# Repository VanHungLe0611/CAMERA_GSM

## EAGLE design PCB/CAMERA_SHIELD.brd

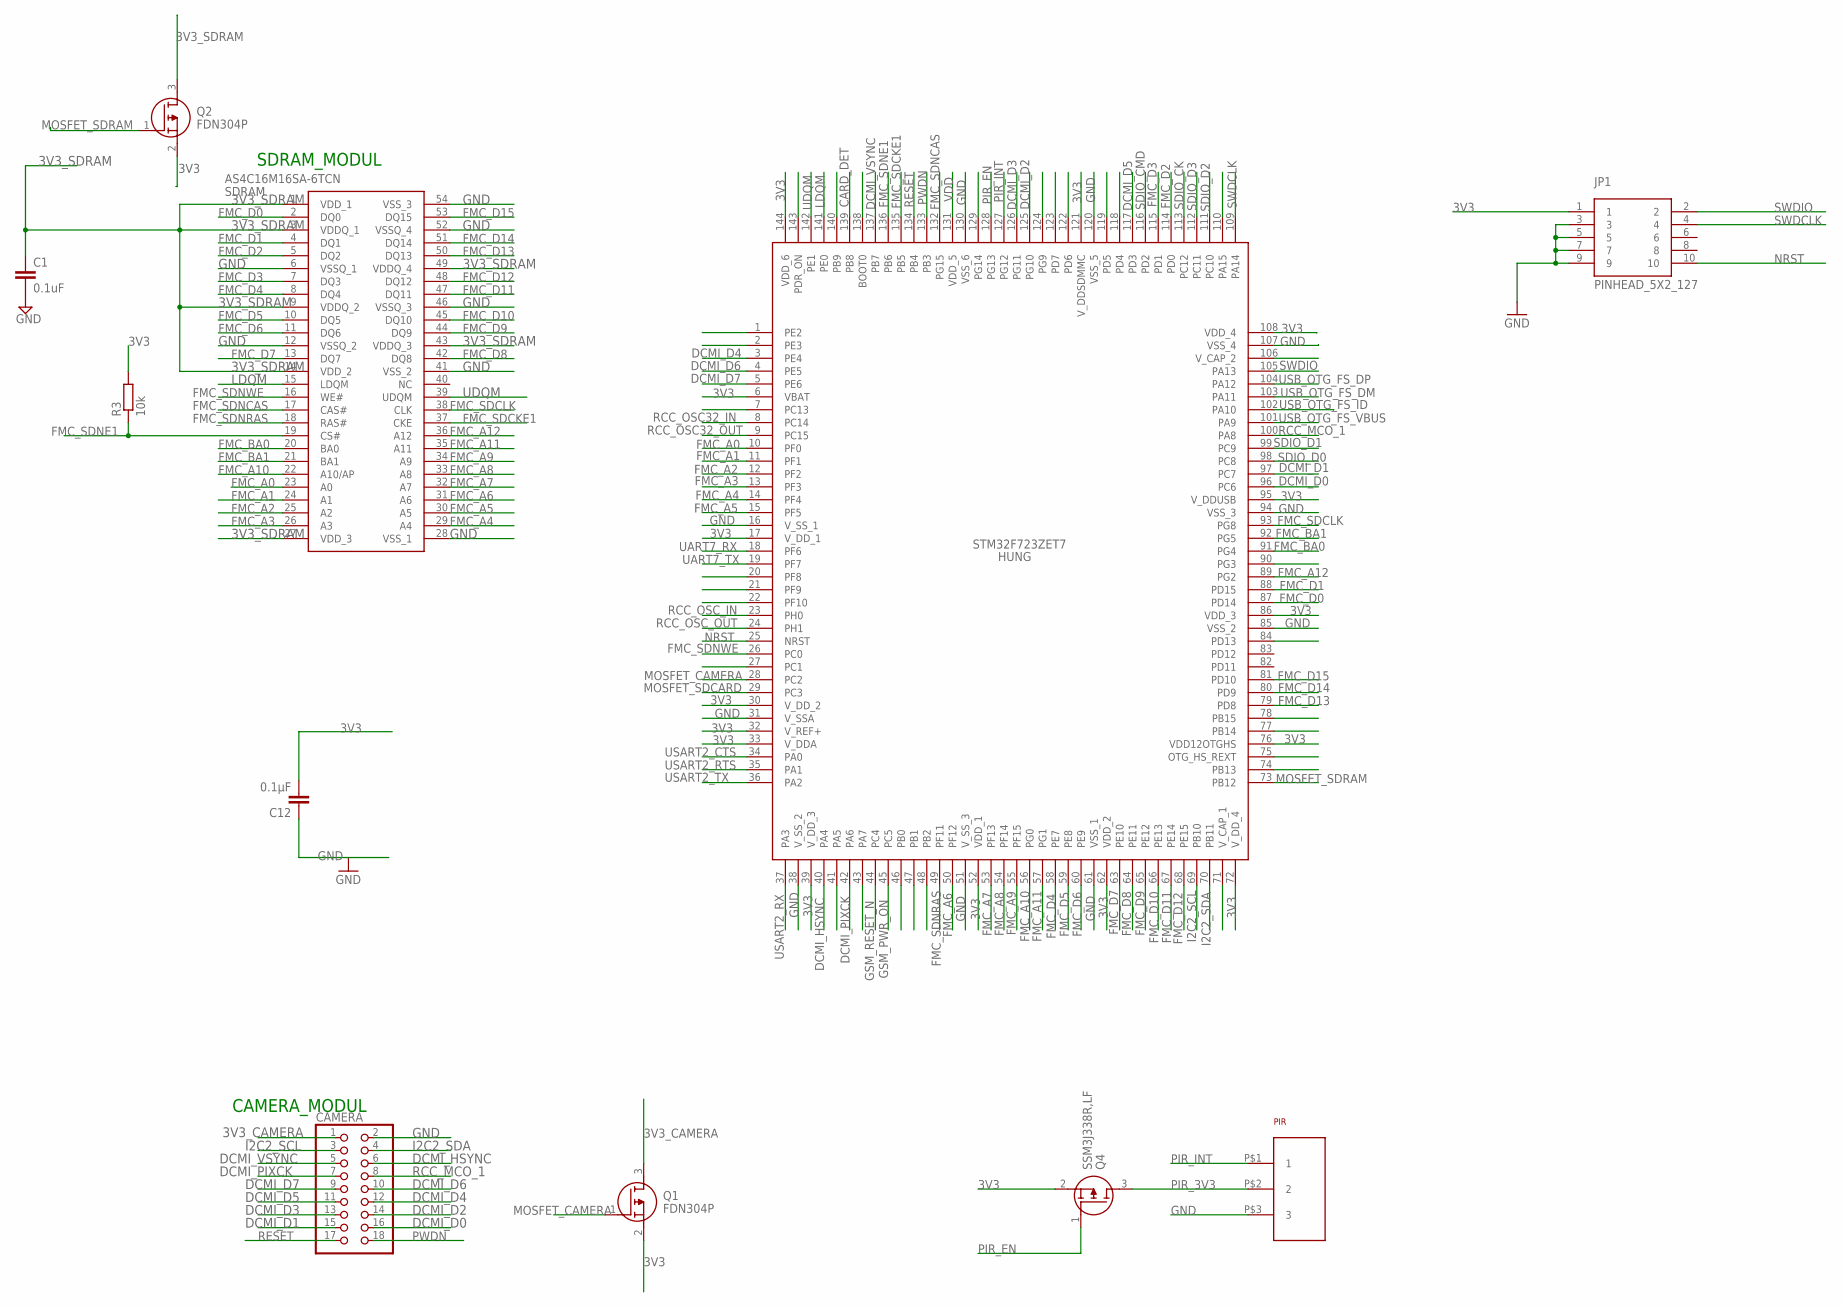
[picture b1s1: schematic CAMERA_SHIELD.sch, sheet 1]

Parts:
C1: 0.1uF; C0402K
C12: 0.1µF; C0402K
CAMERA: 0; 2X09
HUNG: STM32F723ZET7; QFP50P2200X2200X160-144N
JP1: PINHEAD_5X2_127; PINHEAD_2X5_127
PIR: SENBA_PIR_3PIN; SENBA_PIR
Q1, Q2: FDN304P; SOT95P237X112-3N
Q4: SSM3J338R,LF; SSM3J332RLFT
R3: 10k; C0402K
SDRAM: AS4C16M16SA-6TCN; SOP80P1176X120-54N

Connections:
3V3: C12.2, HUNG.6 (VBAT), HUNG.17 (V_DD_1), HUNG.30 (V_DD_2), HUNG.32 (V_REF+), HUNG.33 (V_DDA), HUNG.39 (V_DD_3), HUNG.52 (VDD_1), HUNG.62 (VDD_2), HUNG.72 (V_DD_4), HUNG.76 (VDD12OTGHS), HUNG.86 (VDD_3), HUNG.95 (V_DDUSB), HUNG.108 (VDD_4), HUNG.121 (V_DDSDMMC), HUNG.144 (VDD_6), JP1.1, Q1.2 (S), Q2.2 (S), Q4.2 (S), R3.2; also elsewhere on the board
3V3_CAMERA: CAMERA.1, Q1.3 (D)
3V3_SDRAM: C1.1, Q2.3 (D), SDRAM.1 (VDD_1), SDRAM.3 (VDDQ_1), SDRAM.9 (VDDQ_2), SDRAM.14 (VDD_2), SDRAM.27 (VDD_3), SDRAM.43 (VDDQ_3), SDRAM.49 (VDDQ_4)
CARD_DET: HUNG.139 (PB8); also elsewhere on the board
DCMI_D0: CAMERA.16, HUNG.96 (PC6)
DCMI_D1: CAMERA.15, HUNG.97 (PC7)
DCMI_D2: CAMERA.14, HUNG.125 (PG10)
DCMI_D3: CAMERA.13, HUNG.126 (PG11)
DCMI_D4: CAMERA.12, HUNG.3 (PE4)
DCMI_D5: CAMERA.11, HUNG.117 (PD3)
DCMI_D6: CAMERA.10, HUNG.4 (PE5)
DCMI_D7: CAMERA.9, HUNG.5 (PE6)
DCMI_HSYNC: CAMERA.6, HUNG.40 (PA4)
DCMI_PIXCK: CAMERA.7, HUNG.42 (PA6)
DCMI_VSYNC: CAMERA.5, HUNG.137 (PB7)
FMC_A0: HUNG.10 (PF0), SDRAM.23 (A0)
FMC_A1: HUNG.11 (PF1), SDRAM.24 (A1)
FMC_A2: HUNG.12 (PF2), SDRAM.25 (A2)
FMC_A3: HUNG.13 (PF3), SDRAM.26 (A3)
FMC_A4: HUNG.14 (PF4), SDRAM.29 (A4)
FMC_A5: HUNG.15 (PF5), SDRAM.30 (A5)
FMC_A6: HUNG.50 (PF12), SDRAM.31 (A6)
FMC_A7: HUNG.53 (PF13), SDRAM.32 (A7)
FMC_A8: HUNG.54 (PF14), SDRAM.33 (A8)
FMC_A9: HUNG.55 (PF15), SDRAM.34 (A9)
FMC_A10: HUNG.56 (PG0), SDRAM.22 (A10/AP)
FMC_A11: HUNG.57 (PG1), SDRAM.35 (A11)
FMC_A12: HUNG.89 (PG2), SDRAM.36 (A12)
FMC_BA0: HUNG.91 (PG4), SDRAM.20 (BA0)
FMC_BA1: HUNG.92 (PG5), SDRAM.21 (BA1)
FMC_D0: HUNG.87 (PD14), SDRAM.2 (DQ0)
FMC_D1: HUNG.88 (PD15), SDRAM.4 (DQ1)
FMC_D2: HUNG.114 (PD0), SDRAM.5 (DQ2)
FMC_D3: HUNG.115 (PD1), SDRAM.7 (DQ3)
FMC_D4: HUNG.58 (PE7), SDRAM.8 (DQ4)
FMC_D5: HUNG.59 (PE8), SDRAM.10 (DQ5)
FMC_D6: HUNG.60 (PE9), SDRAM.11 (DQ6)
FMC_D7: HUNG.63 (PE10), SDRAM.13 (DQ7)
FMC_D8: HUNG.64 (PE11), SDRAM.42 (DQ8)
FMC_D9: HUNG.65 (PE12), SDRAM.44 (DQ9)
FMC_D10: HUNG.66 (PE13), SDRAM.45 (DQ10)
FMC_D11: HUNG.67 (PE14), SDRAM.47 (DQ11)
FMC_D12: HUNG.68 (PE15), SDRAM.48 (DQ12)
FMC_D13: HUNG.79 (PD8), SDRAM.50 (DQ13)
FMC_D14: HUNG.80 (PD9), SDRAM.51 (DQ14)
FMC_D15: HUNG.81 (PD10), SDRAM.53 (DQ15)
FMC_SDCKE1: HUNG.135 (PB5), SDRAM.37 (CKE)
FMC_SDCLK: HUNG.93 (PG8), SDRAM.38 (CLK)
FMC_SDNCAS: HUNG.132 (PG15), SDRAM.17 (CAS#)
FMC_SDNE1: HUNG.136 (PB6), R3.1, SDRAM.19 (CS#)
FMC_SDNRAS: HUNG.49 (PF11), SDRAM.18 (RAS#)
FMC_SDNWE: HUNG.26 (PC0), SDRAM.16 (WE#)
GND: C1.2, C12.1, CAMERA.2, HUNG.16 (V_SS_1), HUNG.31 (V_SSA), HUNG.38 (V_SS_2), HUNG.51 (V_SS_3), HUNG.61 (VSS_1), HUNG.85 (VSS_2), HUNG.94 (VSS_3), HUNG.107 (VSS_4), HUNG.120 (VSS_5), HUNG.130 (VSS_6), JP1.3, JP1.5, JP1.7, JP1.9, PIR.P$3 (3), SDRAM.6 (VSSQ_1), SDRAM.12 (VSSQ_2), SDRAM.28 (VSS_1), SDRAM.41 (VSS_2), SDRAM.46 (VSSQ_3), SDRAM.52 (VSSQ_4), SDRAM.54 (VSS_3); also elsewhere on the board
GSM_PWR_ON: HUNG.45 (PC5); also elsewhere on the board
GSM_RESET_N: HUNG.44 (PC4); also elsewhere on the board
I2C2_SCL: CAMERA.3, HUNG.69 (PB10); also elsewhere on the board
I2C2_SDA: CAMERA.4, HUNG.70 (PB11); also elsewhere on the board
LDQM: HUNG.141 (PE0), SDRAM.15 (LDQM)
MOSFET_CAMERA: HUNG.28 (PC2), Q1.1 (G)
MOSFET_SDCARD: HUNG.29 (PC3); also elsewhere on the board
MOSFET_SDRAM: HUNG.73 (PB12), Q2.1 (G)
NRST: HUNG.25 (NRST), JP1.10
PIR_3V3: PIR.P$2 (2), Q4.3 (D)
PIR_EN: HUNG.128 (PG13), Q4.1 (G)
PIR_INT: HUNG.127 (PG12), PIR.P$1 (1)
PWDN: CAMERA.18, HUNG.133 (PB3)
RCC_MCO_1: CAMERA.8, HUNG.100 (PA8)
RCC_OSC32_IN: HUNG.8 (PC14); also elsewhere on the board
RCC_OSC32_OUT: HUNG.9 (PC15); also elsewhere on the board
RCC_OSC_IN: HUNG.23 (PH0); also elsewhere on the board
RCC_OSC_OUT: HUNG.24 (PH1); also elsewhere on the board
RESET: CAMERA.17, HUNG.134 (PB4)
SDIO_CK: HUNG.113 (PC12); also elsewhere on the board
SDIO_CMD: HUNG.116 (PD2); also elsewhere on the board
SDIO_D0: HUNG.98 (PC8); also elsewhere on the board
SDIO_D1: HUNG.99 (PC9); also elsewhere on the board
SDIO_D2: HUNG.111 (PC10); also elsewhere on the board
SDIO_D3: HUNG.112 (PC11); also elsewhere on the board
SWDCLK: HUNG.109 (PA14), JP1.4
SWDIO: HUNG.105 (PA13), JP1.2
UART7_RX: HUNG.18 (PF6); also elsewhere on the board
UART7_TX: HUNG.19 (PF7); also elsewhere on the board
UDQM: HUNG.142 (PE1), SDRAM.39 (UDQM)
USART2_CTS: HUNG.34 (PA0); also elsewhere on the board
USART2_RTS: HUNG.35 (PA1); also elsewhere on the board
USART2_RX: HUNG.37 (PA3); also elsewhere on the board
USART2_TX: HUNG.36 (PA2); also elsewhere on the board
USB_OTG_FS_DM: HUNG.103 (PA11); also elsewhere on the board
USB_OTG_FS_DP: HUNG.104 (PA12); also elsewhere on the board
USB_OTG_FS_ID: HUNG.102 (PA10); also elsewhere on the board
USB_OTG_FS_VBUS: HUNG.101 (PA9); also elsewhere on the board
VDD: HUNG.131 (VDD_5)

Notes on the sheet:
SDRAM_MODUL
CAMERA_MODUL

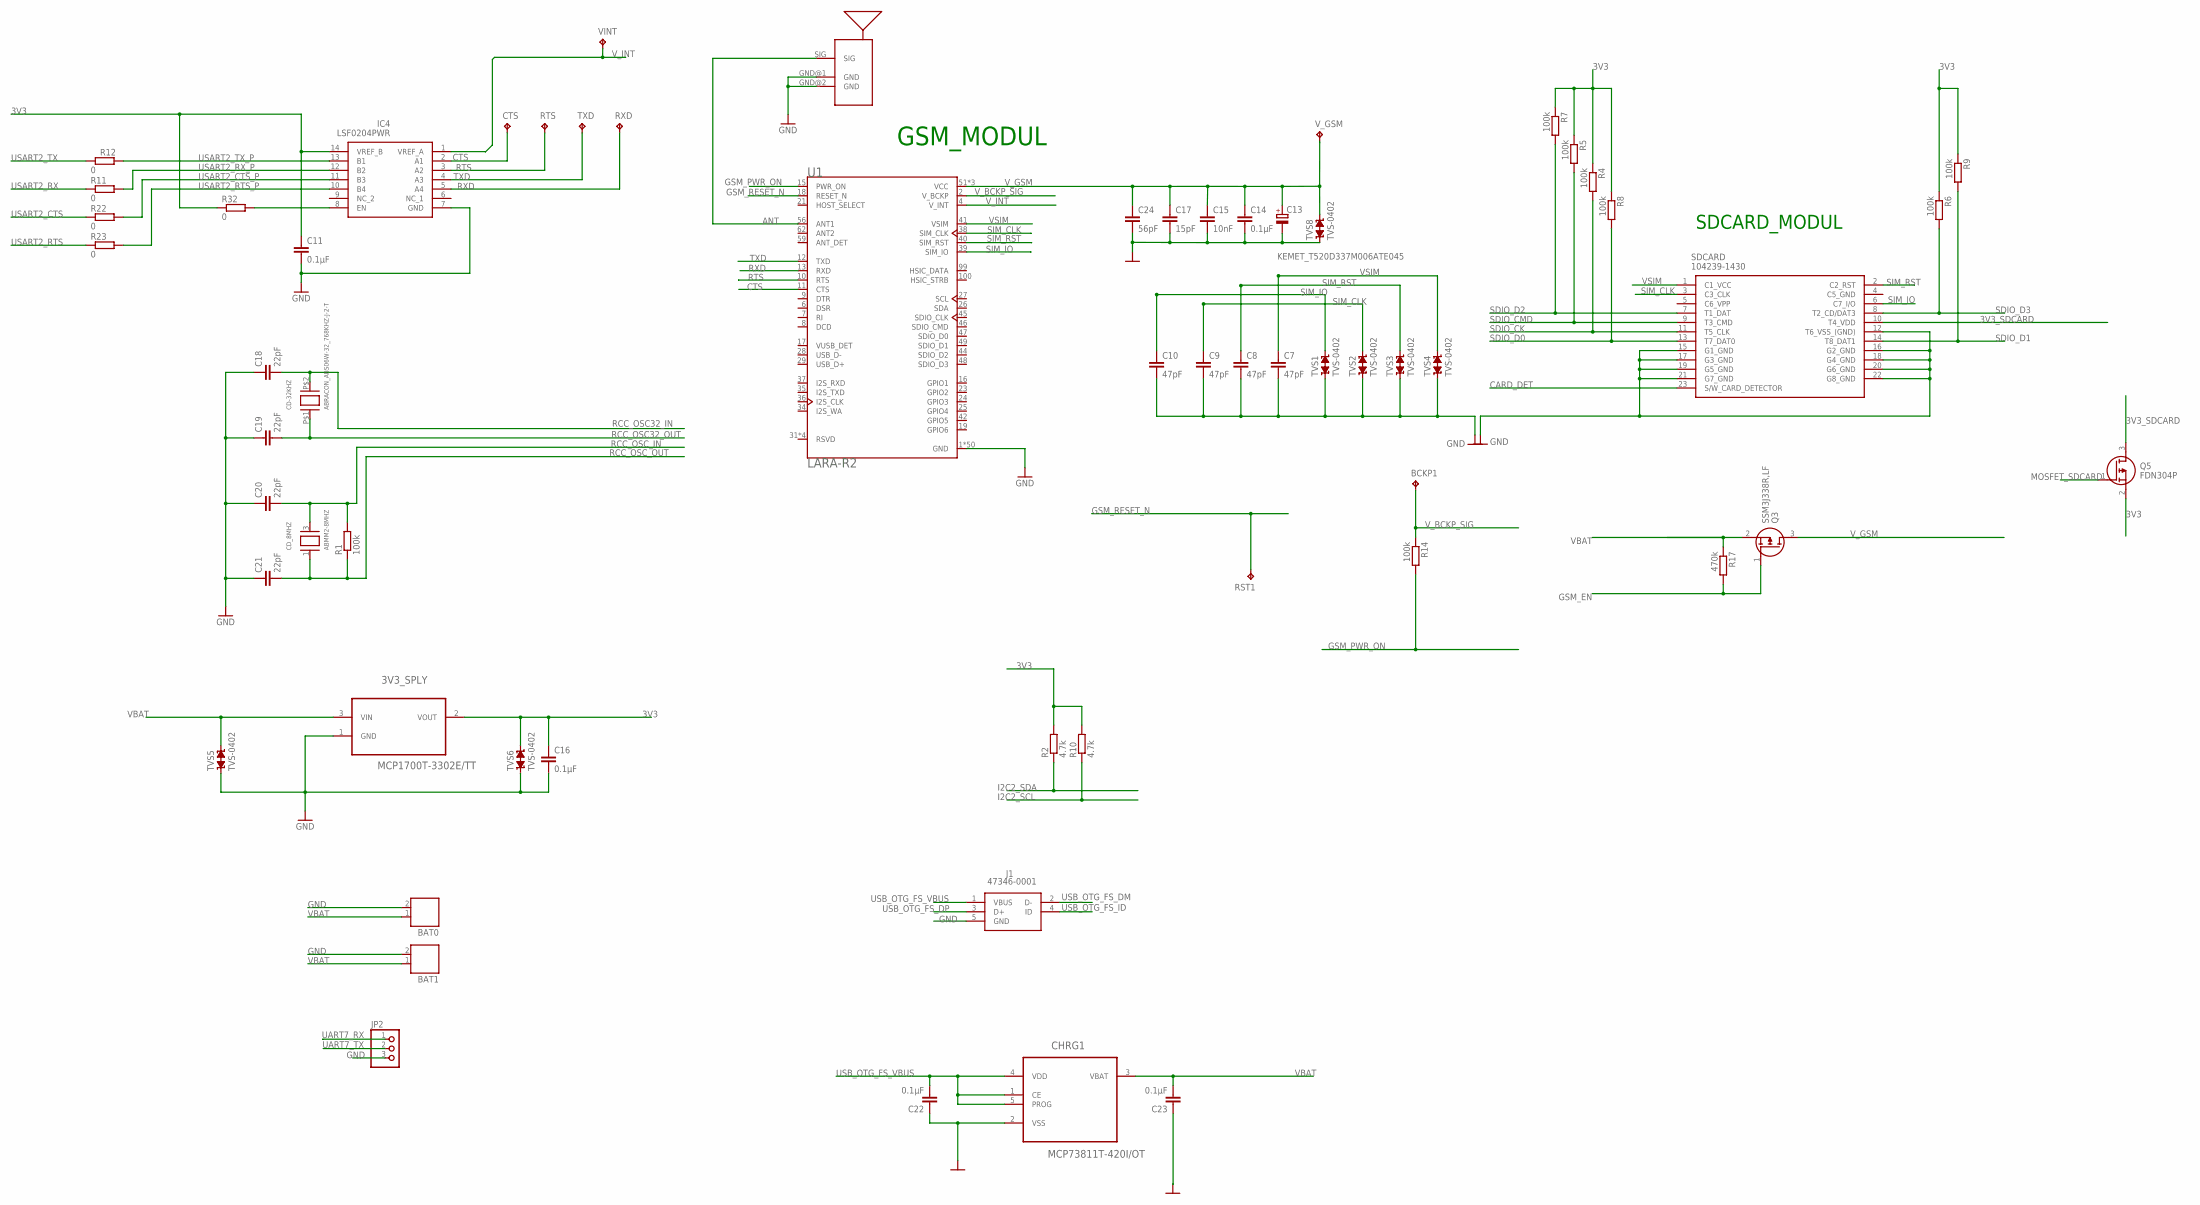
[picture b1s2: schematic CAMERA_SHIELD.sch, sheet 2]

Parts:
3V3_SPLY: MCP1700T-3302E/TT; SOT23
ANT2: U.FL-R-SMT-1; UFL_HIROSE
BAT0, BAT1: JST-PH2
BCKP1: TPB1,27; B1,27
C7, C8, C9, C10: 47pF; C0402K
C11, C14, C16, C22, C23: 0.1µF; C0402K
C13: KEMET_T520D337M006ATE045; 7343_METRIC
C15: 10nF; C0402K
C17: 15pF; C0402K
C18, C19, C20, C21: 22pF; C0402K
C24: 56pF; C0402K
CD-32KHZ: ABRACON_ABS06W-32_768KHZ-J-2-T; 2MM_X_1_2MM
CD_8MHZ: ABMM2-8MHZ; CRYSTAL_ABRACON_6MM_3.6MM
CHRG1: MCP73811T-420I/OT; SOT23-5
CTS: TPB1,27; B1,27
IC4: LSF0204PWR; SOP65P640X120-14N
J1: 47346-0001
JP2: PINHD-1X3; 1X03
Q3: SSM3J338R,LF; SSM3J332RLFT
Q5: FDN304P; SOT95P237X112-3N
R1: 100k; C0402K
R2, R10: 4.7k; C0402K
R4, R5, R6, R7, R8, R9, R14: 100k; R0402
R11, R12, R22, R23: 0; R0402
R17: 470k; R0402
R32: 0; C0402K
RST1: TPB1,27; B1,27
RTS: TPB1,27; B1,27
RXD: TPB1,27; B1,27
SDCARD: 104239-1430; 1042391430
TVS1, TVS2, TVS3, TVS4, TVS5, TVS6, TVS8: TVS-0402; TVS0402
TXD: TPB1,27; B1,27
U1: LARA-R2; XCVR_LARA-R2
VINT: TPB1,27; B1,27
V_GSM: TPB1,27; B1,27

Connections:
3V3: 3V3_SPLY.2 (VOUT), C11.1, C16.1, IC4.14 (VREF_B), Q5.2 (S), R2.2, R4.1, R5.1, R6.1, R7.1, R8.1, R9.1, R10.2, R32.1, TVS6.2; also elsewhere on the board
3V3_SDCARD: Q5.3 (D), SDCARD.10 (T4_VDD)
ANT: ANT2.SIG, U1.56 (ANT1)
CARD_DET: SDCARD.23 (S/W_CARD_DETECTOR); also elsewhere on the board
CTS: CTS.TP, IC4.2 (A1), U1.11 (CTS)
GND: 3V3_SPLY.1 (GND), ANT2.GND@1 (GND), ANT2.GND@2 (GND), BAT0.2, BAT1.2, C7.2, C8.2, C9.2, C10.2, C11.2, C13.-, C14.2, C15.2, C16.2, C17.2, C18.1, C19.1, C20.1, C21.1, C22.1, C23.1, C24.2, CHRG1.2 (VSS), IC4.7 (GND), J1.5 (GND), JP2.3, SDCARD.12 (T6_VSS_(GND)), SDCARD.15 (G1_GND), SDCARD.16 (G2_GND), SDCARD.17 (G3_GND), SDCARD.18 (G4_GND), SDCARD.19 (G5_GND), SDCARD.20 (G6_GND), SDCARD.21 (G7_GND), SDCARD.22 (G8_GND), TVS1.1, TVS2.1, TVS3.1, TVS4.1, TVS5.1, TVS6.1, TVS8.1, U1.1 (GND), U1.3 (GND), U1.5 (GND), U1.14 (GND), U1.20 (GND), U1.22 (GND), U1.30 (GND), U1.32 (GND), U1.43 (GND), U1.50 (GND), U1.54 (GND), U1.55 (GND), U1.57 (GND), U1.58 (GND), U1.60 (GND), U1.61 (GND), U1.63 (GND), U1.64 (GND), U1.65 (GND), U1.66 (GND), U1.67 (GND), U1.68 (GND), U1.69 (GND), U1.70 (GND), U1.71 (GND), U1.72 (GND), U1.73 (GND), U1.74 (GND), U1.75 (GND), U1.76 (GND), U1.77 (GND), U1.78 (GND), U1.79 (GND), U1.80 (GND), U1.81 (GND), U1.82 (GND), U1.83 (GND), U1.84 (GND), U1.85 (GND), U1.86 (GND), U1.87 (GND), U1.88 (GND), U1.89 (GND), U1.90 (GND), U1.91 (GND), U1.92 (GND), U1.93 (GND), U1.94 (GND), U1.95 (GND), U1.96 (GND); also elsewhere on the board
GSM_EN: Q3.1 (G), R17.2
GSM_PWR_ON: R14.2, U1.15 (PWR_ON); also elsewhere on the board
GSM_RESET_N: RST1.TP, U1.18 (RESET_N); also elsewhere on the board
I2C2_SCL: R10.1; also elsewhere on the board
I2C2_SDA: R2.1; also elsewhere on the board
MOSFET_SDCARD: Q5.1 (G); also elsewhere on the board
unnamed: IC4.8 (EN), R32.2
RCC_OSC32_IN: C18.2, CD-32KHZ.P$2 (C1); also elsewhere on the board
RCC_OSC32_OUT: C19.2, CD-32KHZ.P$1 (C0); also elsewhere on the board
RCC_OSC_IN: C20.2, CD_8MHZ.3 (C1), R1.2; also elsewhere on the board
RCC_OSC_OUT: C21.2, CD_8MHZ.1 (C0), R1.1; also elsewhere on the board
RTS: IC4.3 (A2), RTS.TP, U1.10 (RTS)
RXD: IC4.5 (A4), RXD.TP, U1.13 (RXD)
SDIO_CK: R4.2, SDCARD.11 (T5_CLK); also elsewhere on the board
SDIO_CMD: R5.2, SDCARD.9 (T3_CMD); also elsewhere on the board
SDIO_D0: R8.2, SDCARD.13 (T7_DAT0); also elsewhere on the board
SDIO_D1: R9.2, SDCARD.14 (T8_DAT1); also elsewhere on the board
SDIO_D2: R7.2, SDCARD.7 (T1_DAT); also elsewhere on the board
SDIO_D3: R6.2, SDCARD.8 (T2_CD/DAT3); also elsewhere on the board
SIM_CLK: C9.1, SDCARD.3 (C3_CLK), TVS2.2, U1.38 (SIM_CLK)
SIM_IO: C10.1, SDCARD.6 (C7_I/O), TVS1.2, U1.39 (SIM_IO)
SIM_RST: C8.1, SDCARD.2 (C2_RST), TVS3.2, U1.40 (SIM_RST)
TXD: IC4.4 (A3), TXD.TP, U1.12 (TXD)
UART7_RX: JP2.1; also elsewhere on the board
UART7_TX: JP2.2; also elsewhere on the board
USART2_CTS: R22.1; also elsewhere on the board
USART2_CTS_P: IC4.11 (B3), R22.2
USART2_RTS: R23.1; also elsewhere on the board
USART2_RTS_P: IC4.10 (B4), R23.2
USART2_RX: R11.1; also elsewhere on the board
USART2_RX_P: IC4.12 (B2), R11.2
USART2_TX: R12.1; also elsewhere on the board
USART2_TX_P: IC4.13 (B1), R12.2
USB_OTG_FS_DM: J1.2 (D-); also elsewhere on the board
USB_OTG_FS_DP: J1.3 (D+); also elsewhere on the board
USB_OTG_FS_ID: J1.4 (ID); also elsewhere on the board
USB_OTG_FS_VBUS: C22.2, CHRG1.1 (CE), CHRG1.4 (VDD), CHRG1.5 (PROG), J1.1 (VBUS); also elsewhere on the board
VBAT: 3V3_SPLY.3 (VIN), BAT0.1, BAT1.1, C23.2, CHRG1.3 (VBAT), Q3.2 (S), R17.1, TVS5.2
VSIM: C7.1, SDCARD.1 (C1_VCC), TVS4.2, U1.41 (VSIM)
V_BCKP_SIG: BCKP1.TP, R14.1, U1.2 (V_BCKP)
V_GSM: C13.+, C14.1, C15.1, C17.1, C24.1, Q3.3 (D), TVS8.2, U1.51 (VCC), U1.52 (VCC), U1.53 (VCC), V_GSM.TP
V_INT: IC4.1 (VREF_A), U1.4 (V_INT), VINT.TP

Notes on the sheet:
SDCARD_MODUL
GSM_MODUL

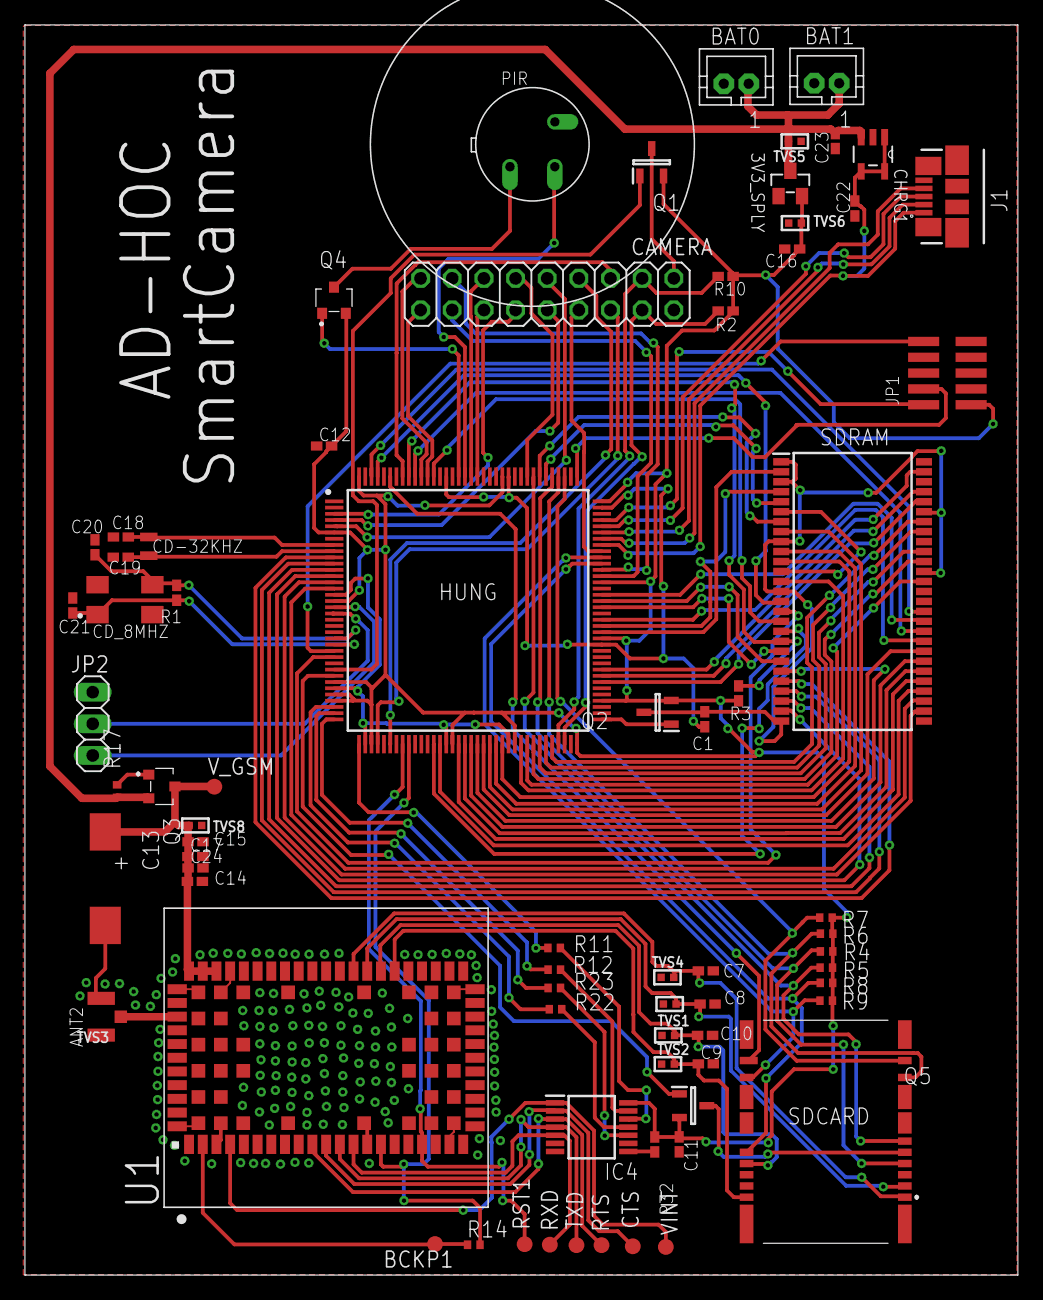
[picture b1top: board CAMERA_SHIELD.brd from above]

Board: 2 copper layers, 79.7 x 100.3 mm, 73 parts (0 on the bottom side), 111 nets.

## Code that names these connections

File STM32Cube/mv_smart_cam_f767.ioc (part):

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Mcu.Name=STM32F767ZITx
Mcu.Package=LQFP144
Mcu.UserName=STM32F767ZITx
PA10.Mode=Slave_8_bits_External_Synchro
PA10.Signal=DCMI_D1
PA11.GPIOParameters=GPIO_Label
PA11.GPIO_Label=USB_DM
PA11.Mode=Device_Only
PA11.Signal=USB_OTG_FS_DM
PA12.GPIOParameters=GPIO_Label
PA12.GPIO_Label=USB_DP
PA12.Mode=Device_Only
PA12.Signal=USB_OTG_FS_DP
PA13.GPIOParameters=GPIO_Label
PA13.GPIO_Label=TMS
PA13.Mode=Serial_Wire
PA13.Signal=SYS_JTMS-SWDIO
PA14.GPIOParameters=GPIO_Label
PA14.GPIO_Label=TCK
PA14.Mode=Serial_Wire
PA14.Signal=SYS_JTCK-SWCLK
PA2.Mode=Asynchronous
PA2.Signal=USART2_TX
PA3.Mode=Asynchronous
PA3.Signal=USART2_RX
PA4.Mode=Slave_8_bits_External_Synchro
PA4.Signal=DCMI_HSYNC
PA6.Mode=Slave_8_bits_External_Synchro
PA6.Signal=DCMI_PIXCLK
PA8.GPIOParameters=GPIO_Label
PA8.GPIO_Label=CAM_XCLK
PA8.Mode=Clock-out-1
PA8.Signal=RCC_MCO_1
PA9.Mode=Slave_8_bits_External_Synchro
PA9.Signal=DCMI_D0
PB10.Mode=I2C
PB10.Signal=I2C2_SCL
PB11.Mode=I2C
PB11.Signal=I2C2_SDA
PB5.Mode=SdramChipSelect2_1
PB5.Signal=FMC_SDCKE1
PB6.Mode=SdramChipSelect2_1
PB6.Signal=FMC_SDNE1
PB7.Mode=Slave_8_bits_External_Synchro
PB7.Signal=DCMI_VSYNC
PB8.GPIOParameters=GPIO_Label
PB8.GPIO_Label=CARD_DET
PB8.Signal=GPIO_Input
PC0.Signal=FMC_SDNWE
PC10.Mode=SD_4_bits_Wide_bus
PC10.Signal=SDMMC1_D2
PC11.Mode=SD_4_bits_Wide_bus
PC11.Signal=SDMMC1_D3
PC12.Mode=SD_4_bits_Wide_bus
PC12.Signal=SDMMC1_CK
PC13.GPIOParameters=GPIO_Label
PC13.GPIO_Label=USER_Btn [B1]
PC13.Signal=GPXTI13
PC14/OSC32_IN.Signal=RCC_OSC32_IN
PC15/OSC32_OUT.Signal=RCC_OSC32_OUT
PC4.GPIOParameters=GPIO_Label
PC4.GPIO_Label=GSM_RESET_N
PC4.Signal=GPIO_Output
PC5.GPIOParameters=GPIO_Label
PC5.GPIO_Label=GSM_PWR_ON
PC5.Signal=GPIO_Output
PC8.Mode=SD_4_bits_Wide_bus
PC8.Signal=SDMMC1_D0
PC9.Mode=SD_4_bits_Wide_bus
PC9.Signal=SDMMC1_D1
PD0.Signal=FMC_D2_DA2
PD1.Signal=FMC_D3_DA3
PD10.Signal=FMC_D15_DA15
PD14.Signal=FMC_D0_DA0
PD15.Signal=FMC_D1_DA1
PD2.Mode=SD_4_bits_Wide_bus
PD2.Signal=SDMMC1_CMD
PD3.Mode=Slave_8_bits_External_Synchro
PD3.Signal=DCMI_D5
PD8.Signal=FMC_D13_DA13
PD9.Signal=FMC_D14_DA14
PE0.Signal=FMC_NBL0
PE1.Signal=FMC_NBL1
PE10.Signal=FMC_D7_DA7
PE11.Signal=FMC_D8_DA8
PE12.Signal=FMC_D9_DA9
PE13.Signal=FMC_D10_DA10
PE14.Signal=FMC_D11_DA11
PE15.Signal=FMC_D12_DA12
PE4.Mode=Slave_8_bits_External_Synchro
PE4.Signal=DCMI_D4
PE5.Mode=Slave_8_bits_External_Synchro
PE5.Signal=DCMI_D6
PE6.Mode=Slave_8_bits_External_Synchro
PE6.Signal=DCMI_D7
PE7.Signal=FMC_D4_DA4
PE8.Signal=FMC_D5_DA5
PE9.Signal=FMC_D6_DA6
PF0.Signal=FMC_A0
PF1.Signal=FMC_A1
PF11.Signal=FMC_SDNRAS
PF12.Signal=FMC_A6
PF13.Signal=FMC_A7
PF14.Signal=FMC_A8
PF15.Signal=FMC_A9
PF2.Signal=FMC_A2
PF3.Signal=FMC_A3
PF4.Signal=FMC_A4
PF5.Signal=FMC_A5
PG0.Signal=FMC_A10
PG1.Signal=FMC_A11
PG10.Mode=Slave_8_bits_External_Synchro
PG10.Signal=DCMI_D2
PG11.Mode=Slave_8_bits_External_Synchro
PG11.Signal=DCMI_D3
PG12.GPIOParameters=GPIO_Label
PG12.GPIO_Label=PIR_IN
PG12.Signal=GPIO_Input
PG13.GPIOParameters=GPIO_Label
PG13.GPIO_Label=MOSFET_PIR
PG13.Signal=GPIO_Output
PG15.Signal=FMC_SDNCAS
PG2.Signal=FMC_A12
PG4.Signal=FMC_A14_BA0
PG5.Signal=FMC_A15_BA1
PG6.GPIOParameters=GPIO_Label
PG6.GPIO_Label=USB_PowerSwitchOn [STMPS2151STR_EN]
PG6.Signal=GPIO_Output
PG7.GPIOParameters=GPIO_Label
PG7.GPIO_Label=USB_OverCurrent [STMPS2151STR_FAULT]
PG7.Signal=GPIO_Input
PG8.Signal=FMC_SDCLK
PG9.GPIOParameters=PinState,GPIO_Label
PG9.GPIO_Label=MOSFET_CAMERA
PG9.PinState=GPIO_PIN_SET
PG9.Signal=GPIO_Output
PH0/OSC_IN.GPIOParameters=GPIO_Label
PH0/OSC_IN.GPIO_Label=MCO [STM32F103CBT6_PA8]
PH0/OSC_IN.Mode=HSE-External-Oscillator
PH0/OSC_IN.Signal=RCC_OSC_IN
PH1/OSC_OUT.Mode=HSE-External-Oscillator
PH1/OSC_OUT.Signal=RCC_OSC_OUT
RCC.HSE_VALUE=8000000
RCC.SYSCLKFreq_VALUE=168000000
RCC.SYSCLKSource=RCC_SYSCLKSOURCE_PLLCLK
RCC.SYSCLKSourceVirtual=RCC_SYSCLKSOURCE_PLLCLK
board=NUCLEO-F767ZI
boardIOC=true

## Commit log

2019-12-20 camera with gsm lara r2
2019-12-20 new route
2020-01-06 new 1
2020-01-10 route gsm
2020-01-13 stm32f7 with gsm-modul
2020-01-13 fix gsm-modul
2020-01-17 smartcamera with gsm
2020-01-17 fix router
2020-01-17 fix ERC-Fehler
2020-01-17 fix power-pins

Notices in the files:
parts and their libraries:
supressor: Copyright (C) 2009, Bob Starr
